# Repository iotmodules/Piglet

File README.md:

# Piglet - IOT Development Module

#Features of the Piglet IOT development board
 
 * ATMega328-au fully compatible with the Arduino IDE
 * Support for Optiboot and DualOptiboot Bootloaders
 * Extremely low power consumption when asleep typically 8uA
 * External 8Mhz crystal oscillator to allow support for the critical timing required by the LORA radios and the LMIC LoRaWAN Library https://github.com/matthijskooijman/arduino-lmic
 * Precision resistor divider to accurately measure the battery voltage before the regulator
 * Real time clock with temperature compensation to provide a high level of accuaracy for time critical functions such as scheduling of transmissions and timestamping events. 
 * Support for HopeRF HCW69HCW and RFM95 Lora radios 
 * On board EUI-64 unique ID accesible over the I2C bus
 * On board 4Mbit SPI flash for configuration data storage and code updates using DualOptiboot 
 * Precision voltage regulator with quiescent current of only 1ua allowing supply voltages between 2.8v and 6.0v
 * U.FL connector for connection of a range of antenna options

#Licence

CC-BY-SA 4.0 https://creativecommons.org/licenses/by-sa/4.0/ You are free to share and adapt. But you need to give attribution and use the same license to redistribute.

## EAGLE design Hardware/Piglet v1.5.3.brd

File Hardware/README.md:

# Piglet

Features of the Piglet IOT development board
 
 * ATMega328-au fully compatible with the Arduino IDE
 * Support for Optiboot and DualOptiboot Bootloaders
 * Extremely low power consumption when asleep typically 8uA
 * External 8Mhz crystal oscillator to allow support for the critical timing required by the LORA radios and the LMIC LoRaWAN Library https://github.com/matthijskooijman/arduino-lmic
 * Precision resistor divider to accurately measure the battery voltage before the regulator
 * Real time clock with temperature compensation to provide a high level of accuaracy for time critical functions such as scheduling of transmissions and timestamping events. 
 * Support for HopeRF HCW69HCW and RFM95 Lora radios 
 * On board EUI-64 unique ID accesible over the I2C bus
 * On board 4Mbit SPI flash for configuration data storage and code updates using DualOptiboot 
 * Precision voltage regulator with quiescent current of only 1ua allowing supply voltages between 2.8v and 6.0v
 * U.FL connector for connection of a range of antenna options

#Licence

CC-BY-SA 4.0 https://creativecommons.org/licenses/by-sa/4.0/ You are free to share and adapt. But you need to give attribution and use the same license to redistribute.

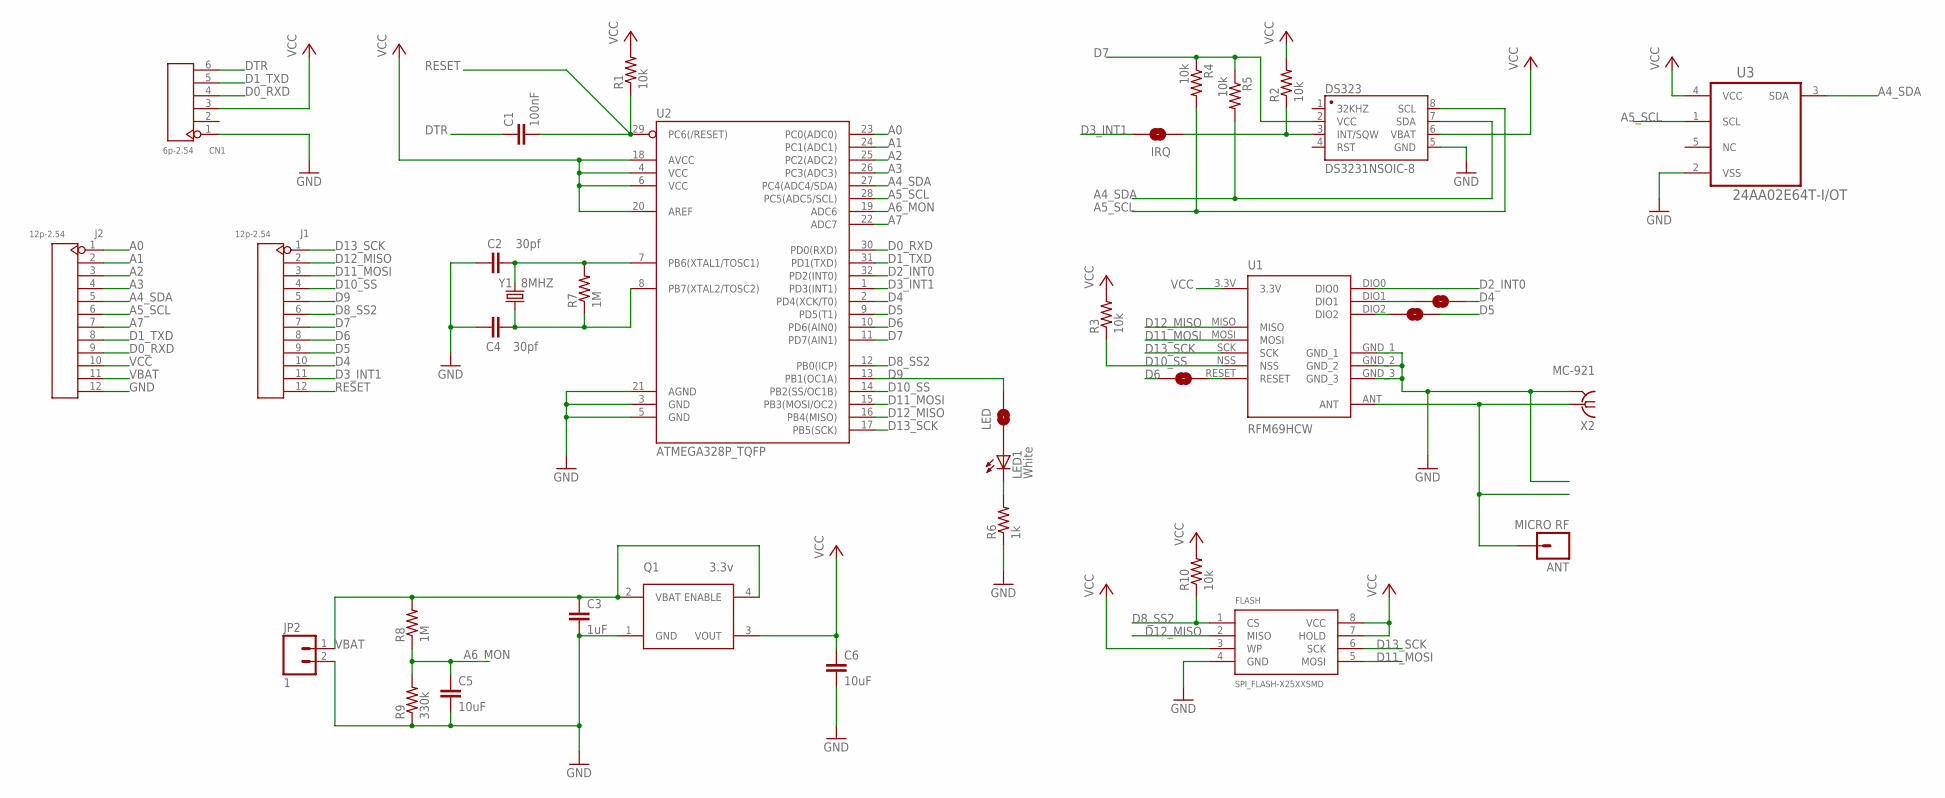
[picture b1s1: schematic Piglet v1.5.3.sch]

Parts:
ANT: MICRO RF; 1X01
C1: 100nF; 0805
C2, C4: 30pf; 0805
C3: 1uF; 0805
C5, C6: 10uF; 0805
CN1: 6p-2.54; H6-2.54
DS323: DS3231NSOIC-8; DS3231MZ+TRL
FLASH: SPI_FLASH-X25XXSMD; SO08
IRQ, IRQ0, IRQ1, IRQ2: SOLDERJUMPERNO; SJ_2S-NO
J1, J2: 12p-2.54; H12-2.54
JP2: 1; M_JST_90_SMD_2
LED: SOLDERJUMPERNO; SJ_2S-NO
LED1: White; CHIPLED_0805
Q1: 3.3v; SOT143
R1, R2, R3, R4, R5, R10: 10k; 0805
R6: 1k; 0805
R7, R8: 1M; 0805
R9: 330k; 0805
U1: RFM69HCW; RFM69HCW-XXXS2
U2: ATMEGA328P_TQFP; TQFP32-08
U3: 24AA02E64T-I/OT; SOT95P270X145-5N
X2: MC-921
Y1: 8MHZ; CRYSTAL-TXC-7A

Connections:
A0: J2.1, U2.23 (PC0(ADC0))
A1: J2.2, U2.24 (PC1(ADC1))
A2: J2.3, U2.25 (PC2(ADC2))
A3: J2.4, U2.26 (PC3(ADC3))
A4_SDA: DS323.7 (SDA), J2.5, R5.2, U2.27 (PC4(ADC4/SDA)), U3.3 (SDA)
A5_SCL: DS323.8 (SCL), J2.6, R4.2, U2.28 (PC5(ADC5/SCL)), U3.1 (SCL)
A6_MON: C5.1, R8.1, R9.2, U2.19 (ADC6)
A7: J2.7, U2.22 (ADC7)
ANT: ANT.1, U1.ANT, X2.1
D0_RXD: CN1.4, J2.9, U2.30 (PD0(RXD))
D1_TXD: CN1.5, J2.8, U2.31 (PD1(TXD))
D2_INT0: U1.DIO0, U2.32 (PD2(INT0))
D3_INT1: IRQ.2, J1.11, U2.1 (PD3(INT1))
D4: IRQ0.1, J1.10, U2.2 (PD4(XCK/T0))
D5: IRQ2.1, J1.9, U2.9 (PD5(T1))
D6: IRQ1.2, J1.8, U2.10 (PD6(AIN0))
D7: DS323.2 (VCC), J1.7, R4.1, R5.1, U2.11 (PD7(AIN1))
D8_SS2: FLASH.1 (CS), J1.6, R10.1, U2.12 (PB0(ICP))
D9: J1.5, LED.2, U2.13 (PB1(OC1A))
D10_SS: J1.4, R3.1, U1.NSS, U2.14 (PB2(SS/OC1B))
D11_MOSI: FLASH.5 (MOSI), J1.3, U1.MOSI, U2.15 (PB3(MOSI/OC2))
D12_MISO: FLASH.2 (MISO), J1.2, U1.MISO, U2.16 (PB4(MISO))
D13_SCK: FLASH.6 (SCK), J1.1, U1.SCK, U2.17 (PB5(SCK))
DTR: C1.1, CN1.6
GND: C2.1, C3.2, C4.1, C5.2, C6.2, CN1.1, DS323.5 (GND), FLASH.4 (GND), J2.12, JP2.2, Q1.1 (GND), R6.1, R9.1, U1.GND_1, U1.GND_2, U1.GND_3, U2.3 (GND), U2.5 (GND), U2.21 (AGND), U3.2 (VSS), X2.2@1 (GND), X2.2@2 (GND)
unnamed: LED1.C, R6.2
unnamed: IRQ2.2, U1.DIO2
unnamed: DS323.3 (INT/SQW), IRQ.1, R2.1
unnamed: C2.2, R7.2, U2.7 (PB6(XTAL1/TOSC1)), Y1.P$2 (2)
unnamed: C4.2, R7.1, U2.8 (PB7(XTAL2/TOSC2)), Y1.P$1 (1)
unnamed: LED.1, LED1.A
unnamed: IRQ0.2, U1.DIO1
unnamed: IRQ1.1, U1.RESET
RESET: C1.2, J1.12, R1.1, U2.29 (PC6(/RESET))
VBAT: C3.1, J2.11, JP2.1, Q1.2 (VBAT), Q1.4 (ENABLE), R8.2
VCC: C6.1, CN1.3, DS323.6 (VBAT), FLASH.3 (WP), FLASH.7 (HOLD), FLASH.8 (VCC), J2.10, Q1.3 (VOUT), R1.2, R2.2, R3.2, R10.2, U1.3.3V, U2.4 (VCC), U2.6 (VCC), U2.18 (AVCC), U2.20 (AREF), U3.4 (VCC)

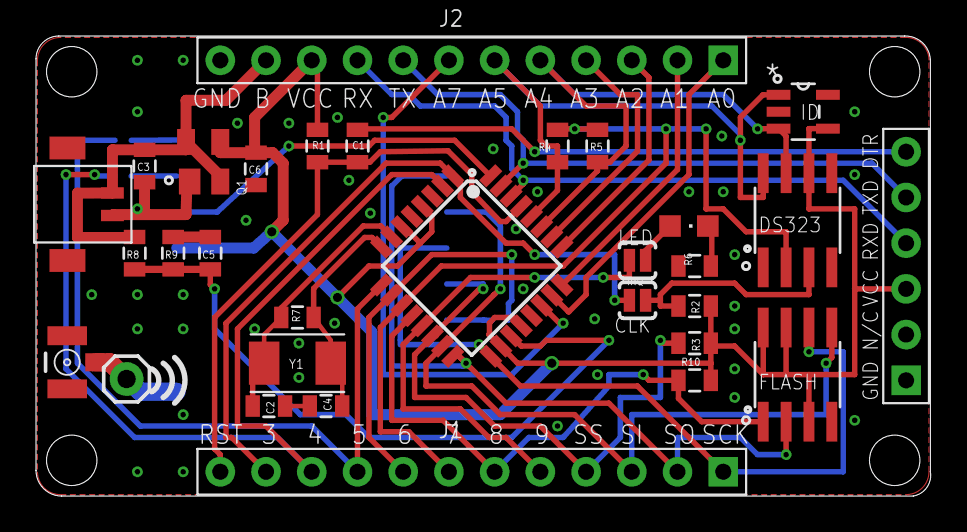
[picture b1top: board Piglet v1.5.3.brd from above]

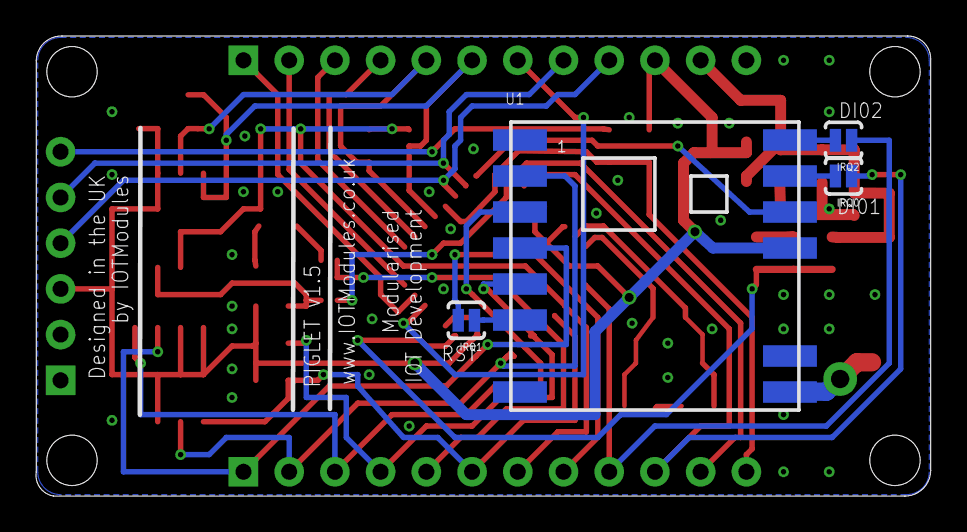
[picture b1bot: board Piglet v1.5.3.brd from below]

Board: 2 copper layers, 49.7 x 25.6 mm, 35 parts (4 on the bottom side), 36 nets.

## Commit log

2017-01-22 Piglet v1.5 MySensors Example
    Added MySensors example demonstrating most of the functionality of the
    hardware.
2017-01-22 Demonstration of the use of the EUI Unique ID for the Piglet v1.5
    Arduino ketch that outputs to the serial port the unique ID of the
    attached piglet.
2017-01-22 Demonstration of the use of the DS3232 real time clock on the Piglet v1.5
    Arduino sketch that outputs to the serial port the time set in setup the
    alarm time and the temperature
2017-01-22 Battery Monitor Example for the Piglet v1.5
    Arduino sketch that reads battery voltage and battery percentage and
    outputs to the serial port
2017-01-22 Updated battery monitor to use external reference
    Using external reference from voltage regulator
2017-01-22 Add readme hardware
2017-01-22 Added licence
2017-01-22 Update of Readme
2017-01-22 Adding Firmware
2017-01-22 Images
2017-01-22 Adding Gerber files
2017-01-22 Board Files
2017-01-23 Adding Hardware Files
2017-01-29 Battery Drain Issue When Lost Connection
    Changed to using static node id
2017-01-29 Battery Dran ods
2017-01-30 Fix rise in battery consumption
    Battery consumption when sleeping now 8.7uA
2017-01-30 Some changes to LED behaviour
    Led flashes quickly 4 times when presentation is requested.
    Flash on TX time reduced to about 33ms

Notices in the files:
parts and their libraries:
SparkFun-Connectors: Licensing: Creative Commons ShareAlike 4.0 International - https://creativecommons.org/licenses/by-sa/4.0
